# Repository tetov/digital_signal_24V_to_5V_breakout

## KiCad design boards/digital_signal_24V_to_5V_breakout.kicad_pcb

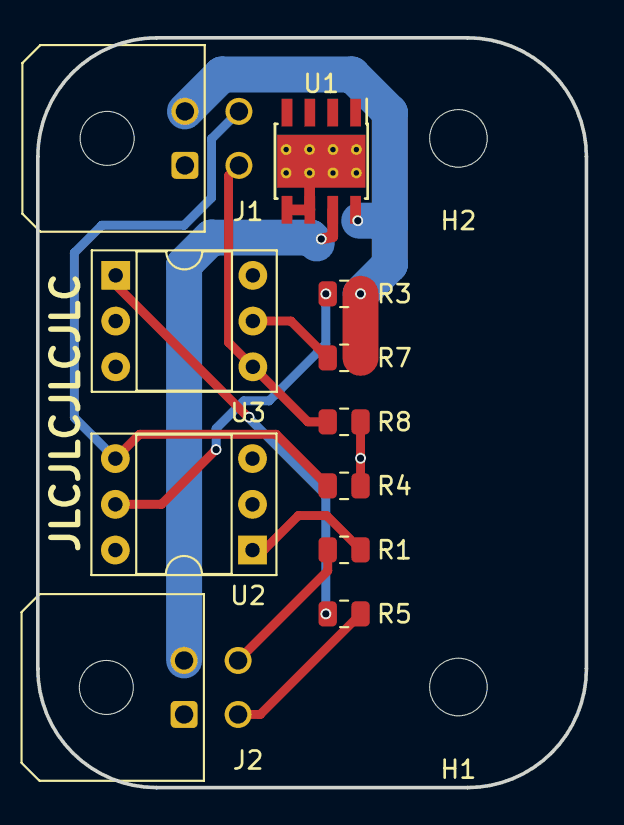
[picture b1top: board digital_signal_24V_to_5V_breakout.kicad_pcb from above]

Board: 4 copper layers, 30.5 x 41.7 mm, 14 parts (1 on the bottom side), 11 nets.

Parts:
H1, H2: MountingHole; MountingHole_3.2mm_M3
J1: Conn_01x04_Male; Molex_Micro-Fit_3.0_43045-0400_2x02_P3.00mm_Horizontal
J2: Conn_01x04_Female; Molex_Micro-Fit_3.0_43045-0400_2x02_P3.00mm_Horizontal
QR*****: qr_repo
R1, R5: 2.7k Ω; R_0805_2012Metric
R3, R7: 100 Ω; R_0805_2012Metric
R4, R8: 4.7 kΩ; R_0805_2012Metric
U1: LM22676MR-ADJ/NOPB; Texas_HSOP-8-1EP_3.9x4.9mm_P1.27mm_ThermalVias
U2, U3: 4N35; DIP-6_W7.62mm_Socket

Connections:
+5V: J1.2, R3.1, R7.1, U1.8 (SW)
+24V: J2.2, U1.7 (VIN)
/Signal A 5V: J1.4, R4.2, U2.4
/Signal A 24V: J2.4, R1.1
/Signal B 5V: J1.3, R8.2, U3.4
/Signal B 24V: J2.3, R5.1
GND: J1.1, J2.1, R4.1, R8.1, U1.5 (EN), U1.6 (GND), U1.9 (EPAD), U2.2, U2.6, U3.2, U3.6
unnamed: R1.2, U2.1
unnamed: R3.2, U2.5
unnamed: R5.2, U3.1
unnamed: R7.2, U3.5

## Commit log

2022-08-03 set up
2022-08-11 ready to upload
2022-08-11 bump actions/images
2022-08-11 fix git error in workflow
2022-08-11 fix git error in workflow 2
2022-08-11 Deploy to GitHub pages
2022-08-11 Create CNAME
